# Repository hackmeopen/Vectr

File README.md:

Vectr
=====

Vectr 3D Sensing Controller

Vectr is an open source 3D sensing controller and sequencer. The board files and firmware are here. Vectr software and hardware are released under 
the Modified BSD License. Vectr uses a number of libraries from Microchip which, although they are free to use,are not fully open source. 
The BSD license allows me to release my contributions as free to use while retaining Microchip's copyrights. This arrangement
was worked out in discussions with the legal department of Microchip.

You are free to use Vectr's firmware and hardware for your own purposes.

Vectr uses Microchip Technology's MGC3130 to sense a user's hand in free space above it's surface. It is able to determine the position of the user's hand within a  cubic volume which is 4inx4inx6in. 

Vectr has 36 LEDs which provide visual feedback about where it senses the user's hand.

It is designed to work with Eurorack modular synthesizers, but the underlying technology can be used for controlling just about anything which will receive an analog voltage input.

Vectr has lots of nifty features for recording sequences of hand movements and playing them back. The sequences can be manipulated as they are played with all sorts of different behaviors. These are the things that make Vectr really special.

So, the code's all there. Vectr uses a PIC32 microcontroller running FreeRTOS. 
There's a lot going on but I've tried to comparmentalize it the best I can. So get started, use it, tweak it, build it!

Cheers

Matt

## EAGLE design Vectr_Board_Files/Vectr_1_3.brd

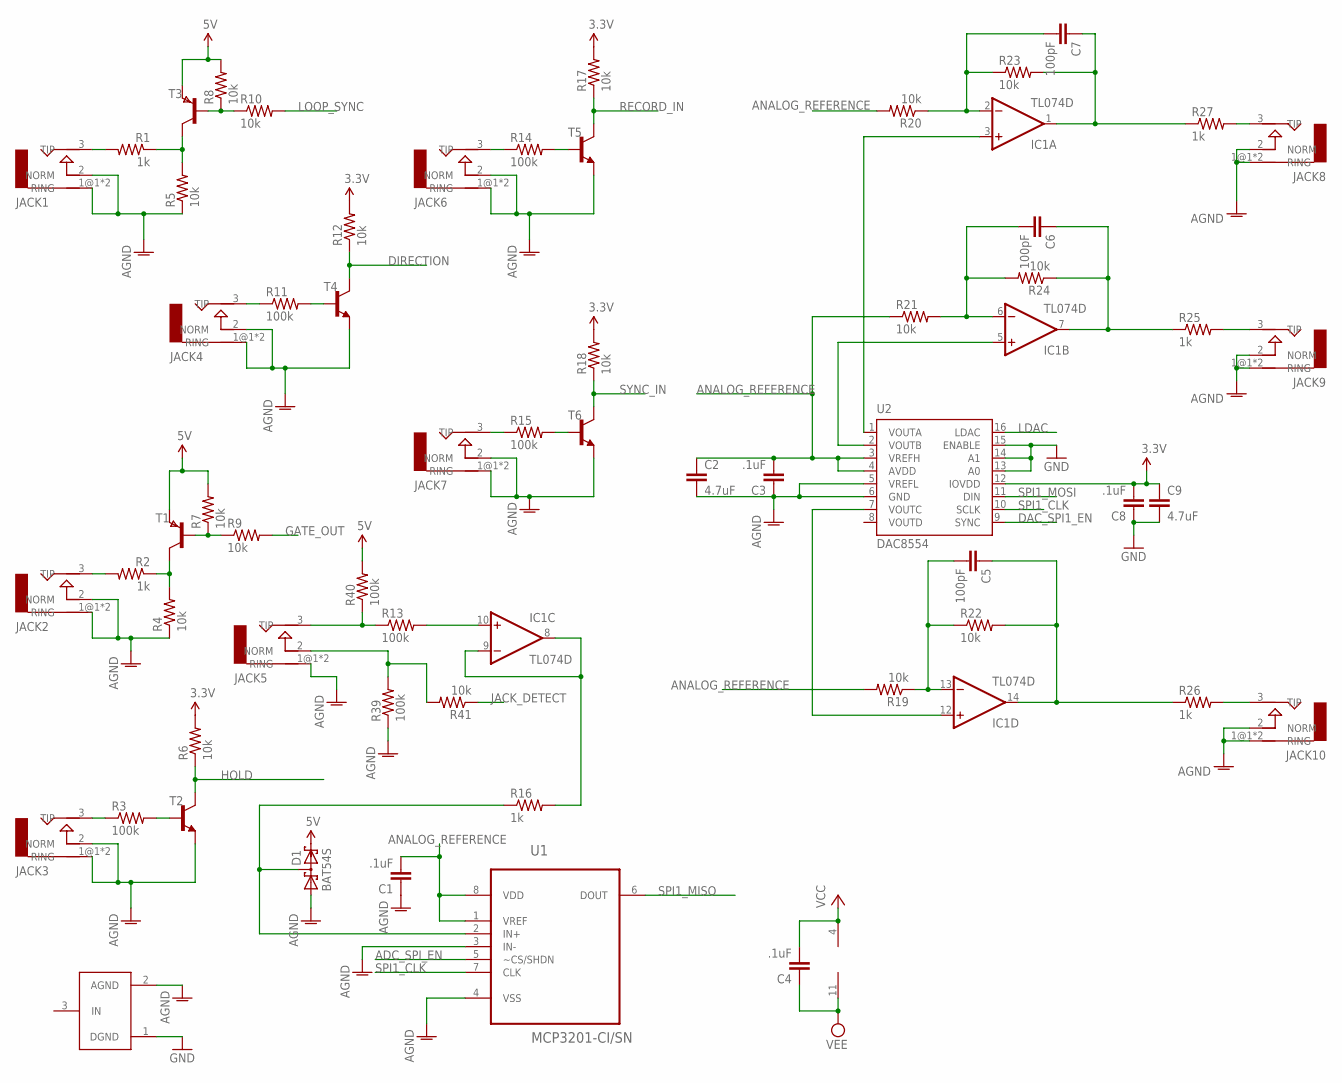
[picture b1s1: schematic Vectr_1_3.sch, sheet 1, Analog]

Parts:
C1, C3, C4, C8: .1uF; 0402-CAP
C2, C9: 4.7uF; 0805
C5, C6, C7: 100pF; 0402-CAP
D1: BAT54S; SOT23
GND_CONNECT: GND_CONNECT
IC1: TL074D; SO14
JACK1, JACK2, JACK3, JACK4, JACK5, JACK6, JACK7, JACK8, JACK9, JACK10: AUDIO-JACKERTHENVAR; ERTHENVAR-JACK
R1, R2, R16, R25, R26, R27: 1k; 0402-RES
R3, R11, R13, R14, R15, R39, R40: 100k; 0402-RES
R4, R5, R6, R7, R8, R9, R10, R12, R17, R18, R19, R20, R21, R22, R23, R24, R41: 10k; 0402-RES
T1, T3: PNPSOT23; SOT-23
T2, T4, T5, T6: TRANSISTOR_NPNSOT23; SOT23
U1: MCP3201-CI/SN; SOIC127P600X175-8N
U2: DAC8554; PW_R-PDSO-G16

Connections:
3.3V: C8.2, C9.1, R6.2, R12.2, R17.2, R18.2, U2.12 (IOVDD); also elsewhere on the board
5V: D1.2 (C2), R7.2, R8.2, R40.2, T1.2 (E), T3.2 (E); also elsewhere on the board
ADC_SPI_EN: U1.5 (~CS/SHDN); also elsewhere on the board
AGND: C1.1, C2.2, C3.1, D1.1 (A1), GND_CONNECT.2 (AGND), JACK1.1@1 (RING), JACK1.1@2 (RING), JACK1.2 (NORM), JACK2.1@1 (RING), JACK2.1@2 (RING), JACK2.2 (NORM), JACK3.1@1 (RING), JACK3.1@2 (RING), JACK3.2 (NORM), JACK4.1@1 (RING), JACK4.1@2 (RING), JACK4.2 (NORM), JACK5.1@1 (RING), JACK5.1@2 (RING), JACK6.1@1 (RING), JACK6.1@2 (RING), JACK6.2 (NORM), JACK7.1@1 (RING), JACK7.1@2 (RING), JACK7.2 (NORM), JACK8.1@1 (RING), JACK8.1@2 (RING), JACK8.2 (NORM), JACK9.1@1 (RING), JACK9.1@2 (RING), JACK9.2 (NORM), JACK10.1@1 (RING), JACK10.1@2 (RING), JACK10.2 (NORM), R4.1, R5.1, R39.1, T2.2 (E), T4.2 (E), T5.2 (E), T6.2 (E), U1.3 (IN-), U1.4 (VSS), U2.5 (VREFL), U2.6 (GND); also elsewhere on the board
ANALOG_REFERENCE: C1.2, C2.1, C3.2, R19.2, R20.2, R21.1, U1.1 (VREF), U1.8 (VDD), U2.3 (VREFH), U2.4 (AVDD); also elsewhere on the board
DAC_SPI1_EN: U2.9 (SYNC); also elsewhere on the board
DIRECTION: R12.1, T4.3 (C); also elsewhere on the board
GATE_OUT: R9.2; also elsewhere on the board
GND: C8.1, C9.2, GND_CONNECT.1 (DGND), U2.13 (A0), U2.14 (A1), U2.15 (ENABLE); also elsewhere on the board
HOLD: R6.1, T2.3 (C); also elsewhere on the board
JACK_DETECT: R41.1; also elsewhere on the board
LDAC: U2.16 (LDAC); also elsewhere on the board
LOOP_SYNC: R10.2; also elsewhere on the board
unnamed: R8.1, R10.1, T3.3 (B)
unnamed: C7.2, IC1.2 (-IN), R20.1, R23.1
unnamed: IC1.10 (+IN), R13.2
unnamed: C7.1, IC1.1 (OUT), R23.2, R27.1
unnamed: R1.1, R5.2, T3.1 (C)
unnamed: JACK1.3 (TIP), R1.2
unnamed: IC1.5 (+IN), U2.2 (VOUTB)
unnamed: JACK4.3 (TIP), R11.1
unnamed: R11.2, T4.1 (B)
unnamed: IC1.8 (OUT), IC1.9 (-IN), R16.2
unnamed: C6.2, IC1.6 (-IN), R21.2, R24.2
unnamed: R7.1, R9.1, T1.3 (B)
unnamed: R2.1, R4.2, T1.1 (C)
unnamed: JACK2.3 (TIP), R2.2
unnamed: C6.1, IC1.7 (OUT), R24.1, R25.1
unnamed: R3.2, T2.1 (B)
unnamed: JACK3.3 (TIP), R3.1
unnamed: C5.2, IC1.13 (-IN), R19.1, R22.1
unnamed: C5.1, IC1.14 (OUT), R22.2, R26.1
unnamed: JACK5.2 (NORM), R39.2, R41.2
unnamed: IC1.3 (+IN), U2.1 (VOUTA)
unnamed: D1.3 (C1A2), R16.1, U1.2 (IN+)
unnamed: JACK8.3 (TIP), R27.2
unnamed: JACK5.3 (TIP), R13.1, R40.1
unnamed: JACK6.3 (TIP), R14.1
unnamed: JACK9.3 (TIP), R25.2
unnamed: R14.2, T5.1 (B)
unnamed: IC1.12 (+IN), U2.7 (VOUTC)
unnamed: JACK10.3 (TIP), R26.2
unnamed: JACK7.3 (TIP), R15.1
unnamed: R15.2, T6.1 (B)
RECORD_IN: R17.1, T5.3 (C); also elsewhere on the board
SPI1_CLK: U1.7 (CLK), U2.10 (SCLK); also elsewhere on the board
SPI1_MISO: U1.6 (DOUT); also elsewhere on the board
SPI1_MOSI: U2.11 (DIN); also elsewhere on the board
SYNC_IN: R18.1, T6.3 (C); also elsewhere on the board
VCC: C4.2, IC1.4 (V+); also elsewhere on the board
VEE: C4.1, IC1.11 (V-); also elsewhere on the board

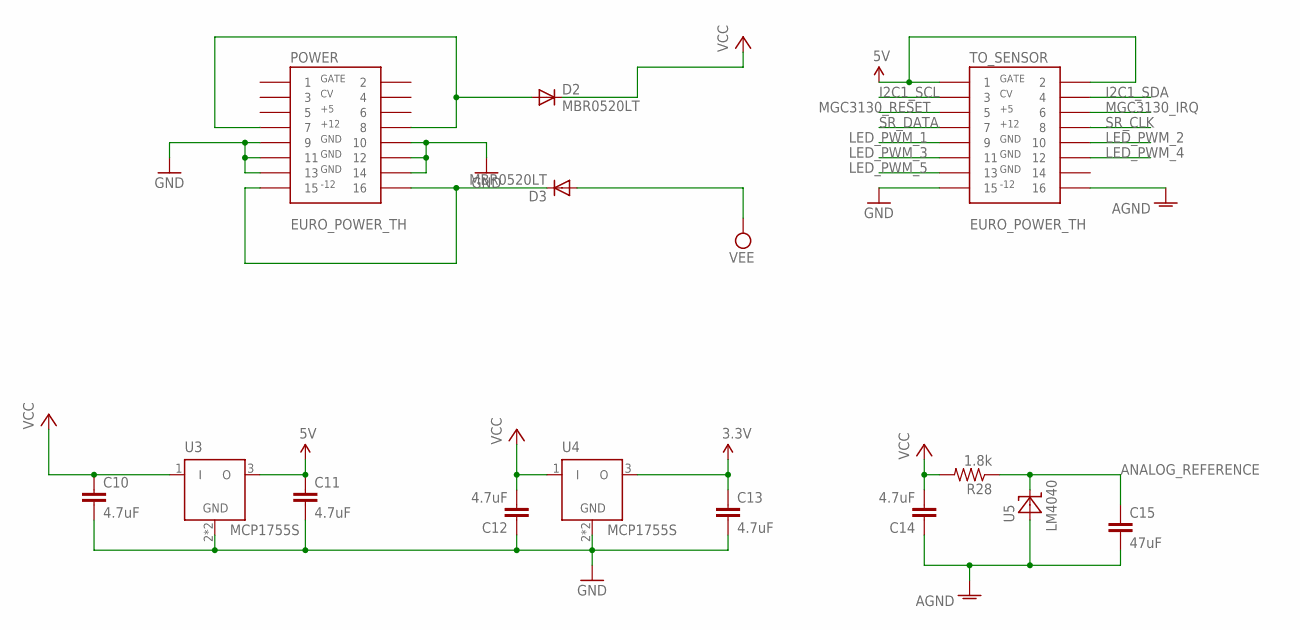
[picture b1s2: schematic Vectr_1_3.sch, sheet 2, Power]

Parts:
C10, C11, C12, C13, C14: 4.7uF; 0805
C15: 47uF; 0805
D2, D3: MBR0520LT; SOD123
POWER: EURO_POWER_TH
R28: 1.8k; 0402-RES
TO_SENSOR: EURO_POWER_TH
U3, U4: MCP1755S; SOT223
U5: LM4040; SOT23

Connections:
3.3V: C13.1, U4.3 (O); also elsewhere on the board
5V: C11.1, TO_SENSOR.1, TO_SENSOR.2, U3.3 (O); also elsewhere on the board
AGND: C14.1, C15.2, TO_SENSOR.16, U5.2 (A); also elsewhere on the board
ANALOG_REFERENCE: C15.1, R28.1, U5.3 (C); also elsewhere on the board
GND: C10.2, C11.2, C12.1, C13.2, POWER.9, POWER.10, POWER.11, POWER.12, POWER.13, POWER.14, TO_SENSOR.15, U3.2 (GND), U3.4 (GND), U4.2 (GND), U4.4 (GND); also elsewhere on the board
I2C1_SCL: TO_SENSOR.3; also elsewhere on the board
I2C1_SDA: TO_SENSOR.4; also elsewhere on the board
LED_PWM_1: TO_SENSOR.9; also elsewhere on the board
LED_PWM_2: TO_SENSOR.10; also elsewhere on the board
LED_PWM_3: TO_SENSOR.11; also elsewhere on the board
LED_PWM_4: TO_SENSOR.12; also elsewhere on the board
LED_PWM_5: TO_SENSOR.13; also elsewhere on the board
MGC3130_IRQ: TO_SENSOR.6; also elsewhere on the board
MGC3130_RESET: TO_SENSOR.5; also elsewhere on the board
unnamed: D2.A, POWER.7, POWER.8
unnamed: D3.C, POWER.15, POWER.16
SR_CLK: TO_SENSOR.8; also elsewhere on the board
SR_DATA: TO_SENSOR.7; also elsewhere on the board
VCC: C10.1, C12.2, C14.2, D2.C, R28.2, U3.1 (I), U4.1 (I); also elsewhere on the board
VEE: D3.A; also elsewhere on the board

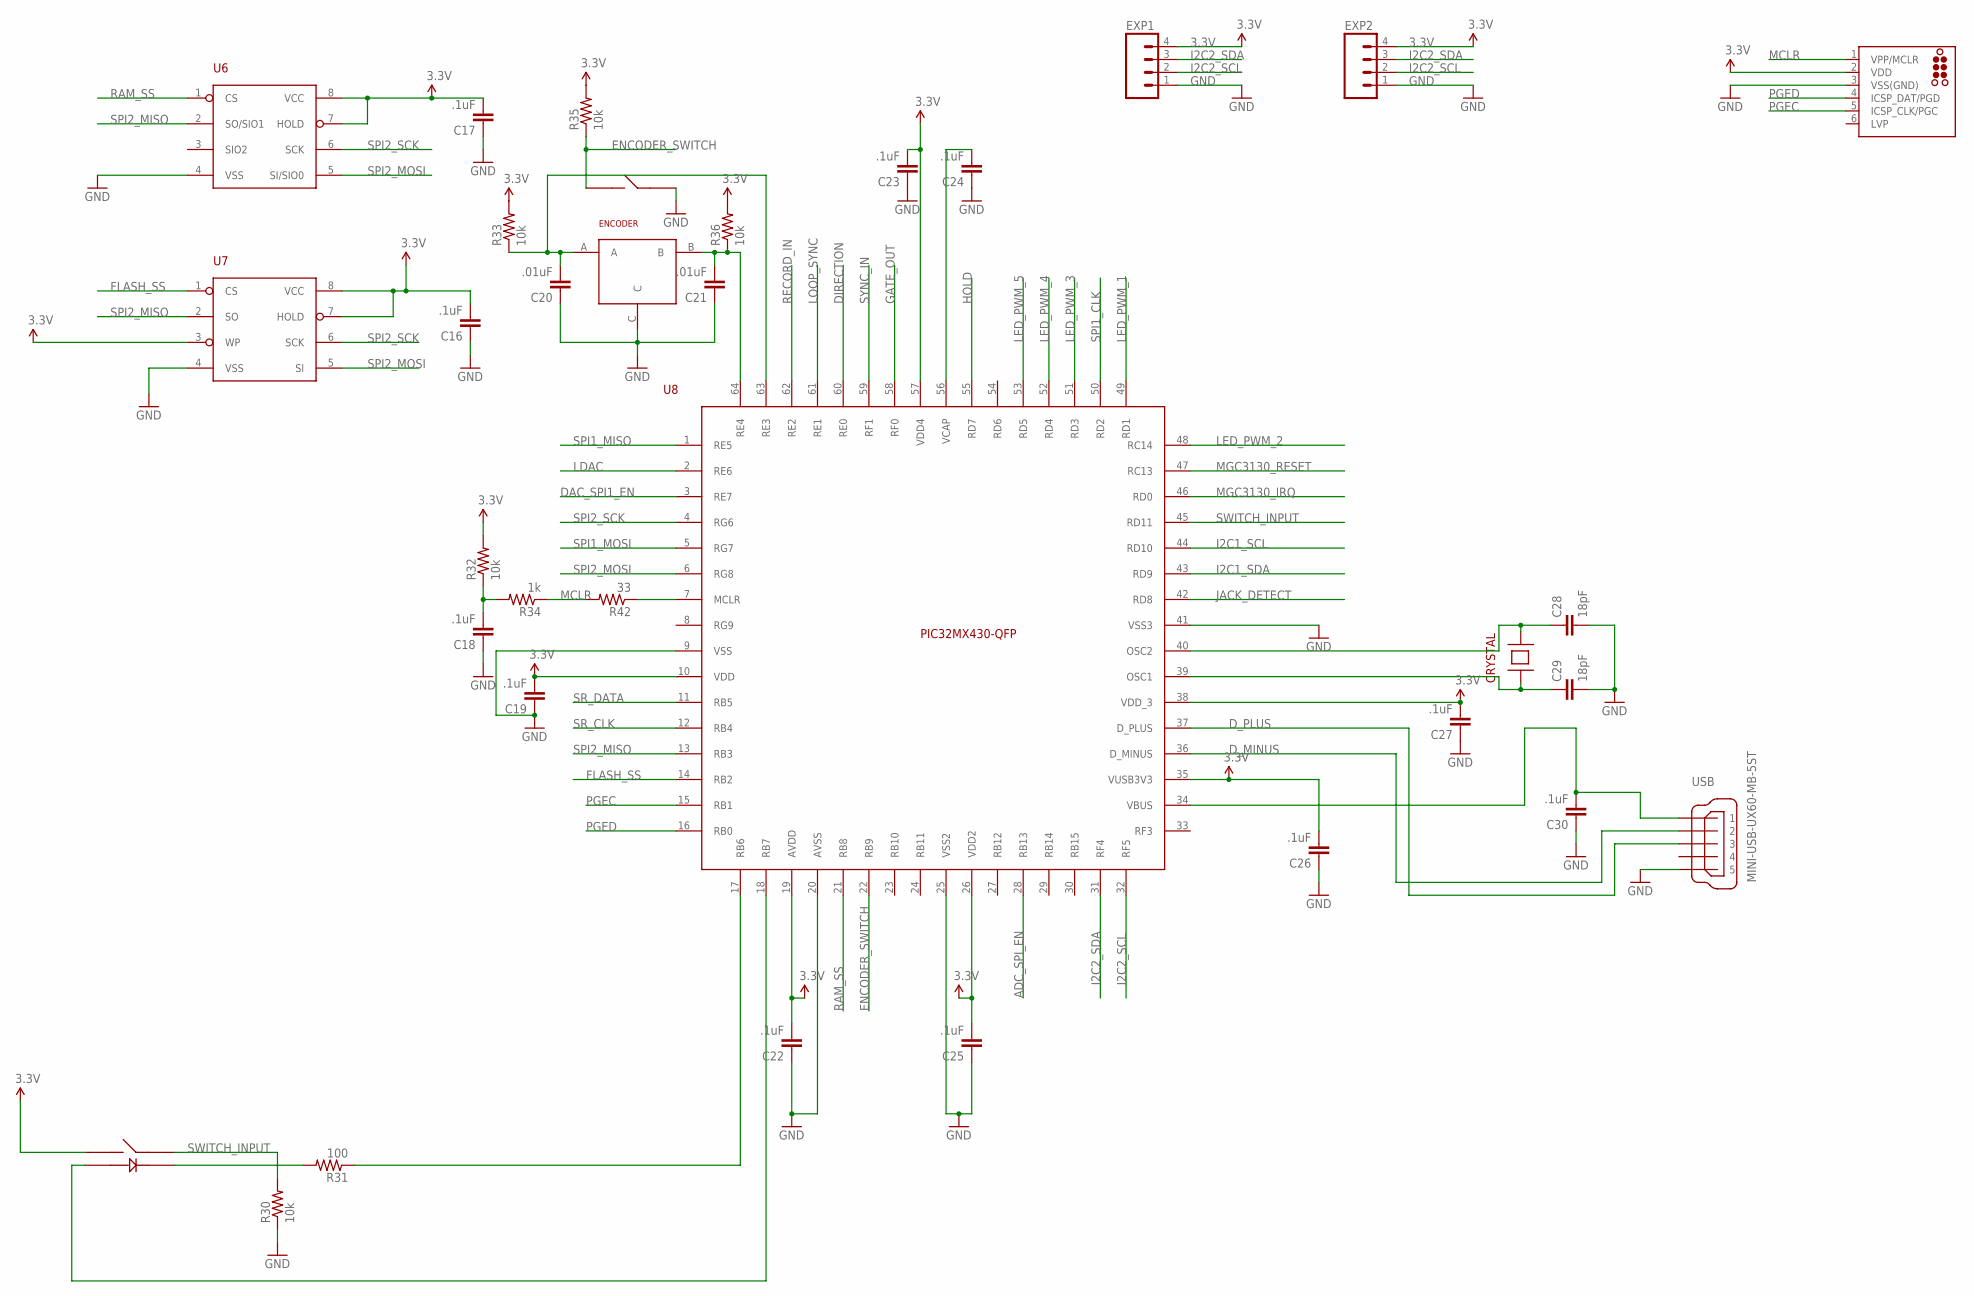
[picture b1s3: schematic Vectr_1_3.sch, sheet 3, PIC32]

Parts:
C16, C17, C18, C19, C22, C23, C24, C25, C26, C27, C30: .1uF; 0402-CAP
C20, C21: .01uF; 0402-CAP
C28, C29: 18pF; 0402-CAP
CRYSTAL: SMD-4-CRYSTAL
ENCODER: PEC16_ENCODER
EXP1, EXP2: M04PTH; 1X04
J1: TC2030-MCP
R30, R32, R33, R35, R36: 10k; 0402-RES
R31: 100; 0402-RES
R34: 1k; 0402-RES
R42: 33; 0402-RES
SWITCH: 5GSH9
U6: 23LC512; SO-08
U7: SST25VF010A; SO-08
U8: PIC32MX430-QFP; QFP50P1200X1200X120-64N
USB: MINI-USB-UX60-MB-5ST; UX60-MB-5ST

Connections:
3.3V: C16.2, C17.2, C19.2, C22.2, C23.2, C25.2, C26.2, C27.2, EXP1.4, EXP2.4, J1.2 (VDD), R32.2, R33.2, R35.2, R36.2, SWITCH.1, U6.7 (HOLD), U6.8 (VCC), U7.3 (WP), U7.7 (HOLD), U7.8 (VCC), U8.10 (VDD), U8.19 (AVDD), U8.26 (VDD2), U8.35 (VUSB3V3), U8.38 (VDD_3), U8.57 (VDD4); also elsewhere on the board
ADC_SPI_EN: U8.28 (RB13); also elsewhere on the board
DAC_SPI1_EN: U8.3 (RE7); also elsewhere on the board
DIRECTION: U8.60 (RE0); also elsewhere on the board
D_MINUS: U8.36 (D_MINUS), USB.2
D_PLUS: U8.37 (D_PLUS), USB.3
ENCODER_SWITCH: ENCODER.D, R35.1, U8.22 (RB9)
FLASH_SS: U7.1 (CS), U8.14 (RB2)
GATE_OUT: U8.58 (RF0); also elsewhere on the board
GND: C16.1, C17.1, C18.1, C19.1, C20.1, C21.1, C22.1, C23.1, C24.1, C25.1, C26.1, C27.1, C28.2, C29.2, C30.1, ENCODER.C, ENCODER.E, EXP1.1, EXP2.1, J1.3 (VSS(GND)), R30.1, U6.4 (VSS), U7.4 (VSS), U8.9 (VSS), U8.20 (AVSS), U8.25 (VSS2), U8.41 (VSS3), USB.5; also elsewhere on the board
HOLD: U8.55 (RD7); also elsewhere on the board
I2C1_SCL: U8.44 (RD10); also elsewhere on the board
I2C1_SDA: U8.43 (RD9); also elsewhere on the board
I2C2_SCL: EXP1.2, EXP2.2, U8.32 (RF5)
I2C2_SDA: EXP1.3, EXP2.3, U8.31 (RF4)
JACK_DETECT: U8.42 (RD8); also elsewhere on the board
LDAC: U8.2 (RE6); also elsewhere on the board
LED_PWM_1: U8.49 (RD1); also elsewhere on the board
LED_PWM_2: U8.48 (RC14); also elsewhere on the board
LED_PWM_3: U8.51 (RD3); also elsewhere on the board
LED_PWM_4: U8.52 (RD4); also elsewhere on the board
LED_PWM_5: U8.53 (RD5); also elsewhere on the board
LOOP_SYNC: U8.61 (RE1); also elsewhere on the board
MCLR: J1.1 (VPP/MCLR), R34.1, R42.2
MGC3130_IRQ: U8.46 (RD0); also elsewhere on the board
MGC3130_RESET: U8.47 (RC13); also elsewhere on the board
unnamed: C18.2, R32.1, R34.2
unnamed: C21.2, ENCODER.B, R36.1, U8.64 (RE4)
unnamed: C20.2, ENCODER.A, R33.1, U8.63 (RE3)
unnamed: SWITCH.3, U8.18 (RB7)
unnamed: C28.1, CRYSTAL.3, U8.40 (OSC2)
unnamed: C29.1, CRYSTAL.1, U8.39 (OSC1)
unnamed: C30.2, U8.34 (VBUS), USB.1
unnamed: C24.2, U8.56 (VCAP)
unnamed: R31.2, SWITCH.2
PGEC: J1.5 (ICSP_CLK/PGC), U8.15 (RB1)
PGED: J1.4 (ICSP_DAT/PGD), U8.16 (RB0)
RAM_SS: U6.1 (CS), U8.21 (RB8)
RECORD_IN: U8.62 (RE2); also elsewhere on the board
RESET: R42.1, U8.7 (MCLR)
SPI1_CLK: U8.50 (RD2); also elsewhere on the board
SPI1_MISO: U8.1 (RE5); also elsewhere on the board
SPI1_MOSI: U8.5 (RG7); also elsewhere on the board
SPI2_MISO: U6.2 (SO/SIO1), U7.2 (SO), U8.13 (RB3)
SPI2_MOSI: U6.5 (SI/SIO0), U7.5 (SI), U8.6 (RG8)
SPI2_SCK: U6.6 (SCK), U7.6 (SCK), U8.4 (RG6)
SR_CLK: U8.12 (RB4); also elsewhere on the board
SR_DATA: U8.11 (RB5); also elsewhere on the board
SWITCH_INPUT: R30.2, SWITCH.4, U8.45 (RD11)
SWITCH_LED1: R31.1, U8.17 (RB6)
SYNC_IN: U8.59 (RF1); also elsewhere on the board

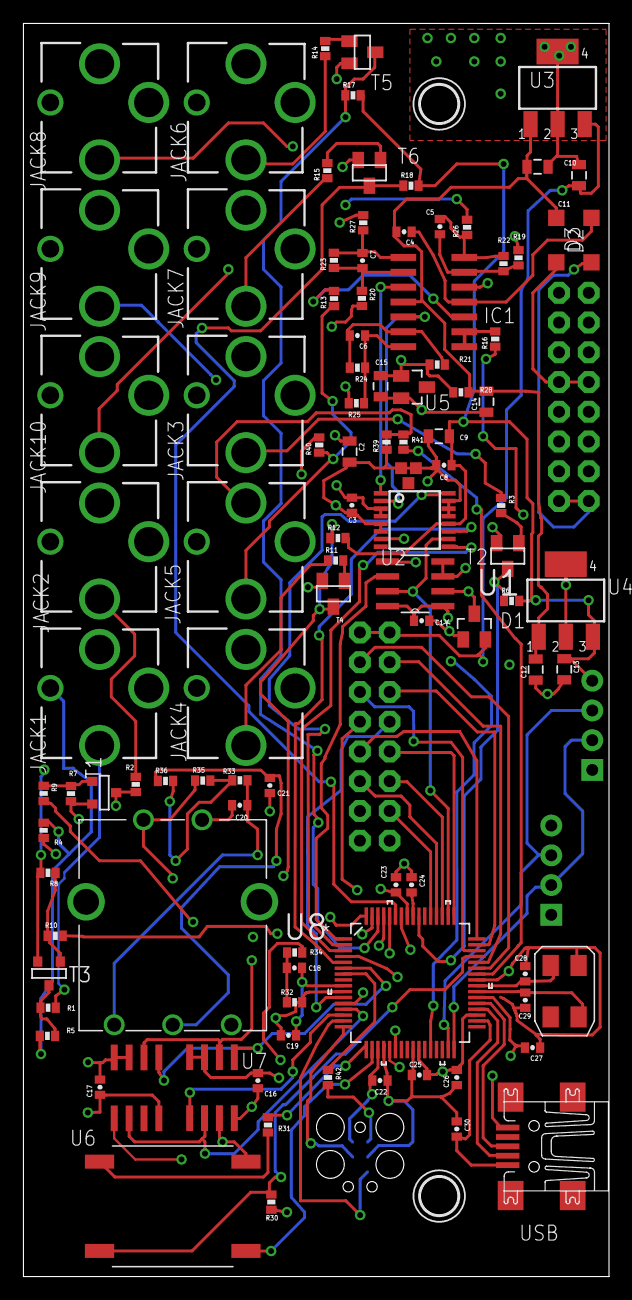
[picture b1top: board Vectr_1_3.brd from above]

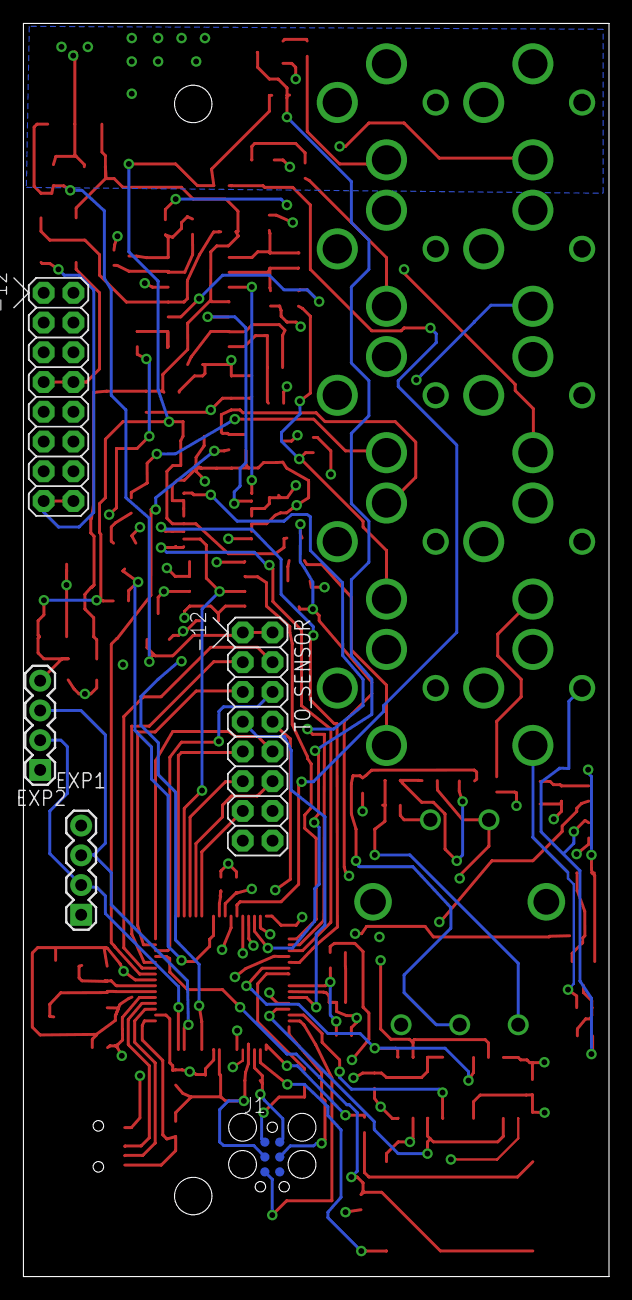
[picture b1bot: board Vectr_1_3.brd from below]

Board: 4 copper layers, 50.0 x 107.0 mm, 109 parts (5 on the bottom side), 89 nets.

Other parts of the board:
U$3, U$5: 3,2

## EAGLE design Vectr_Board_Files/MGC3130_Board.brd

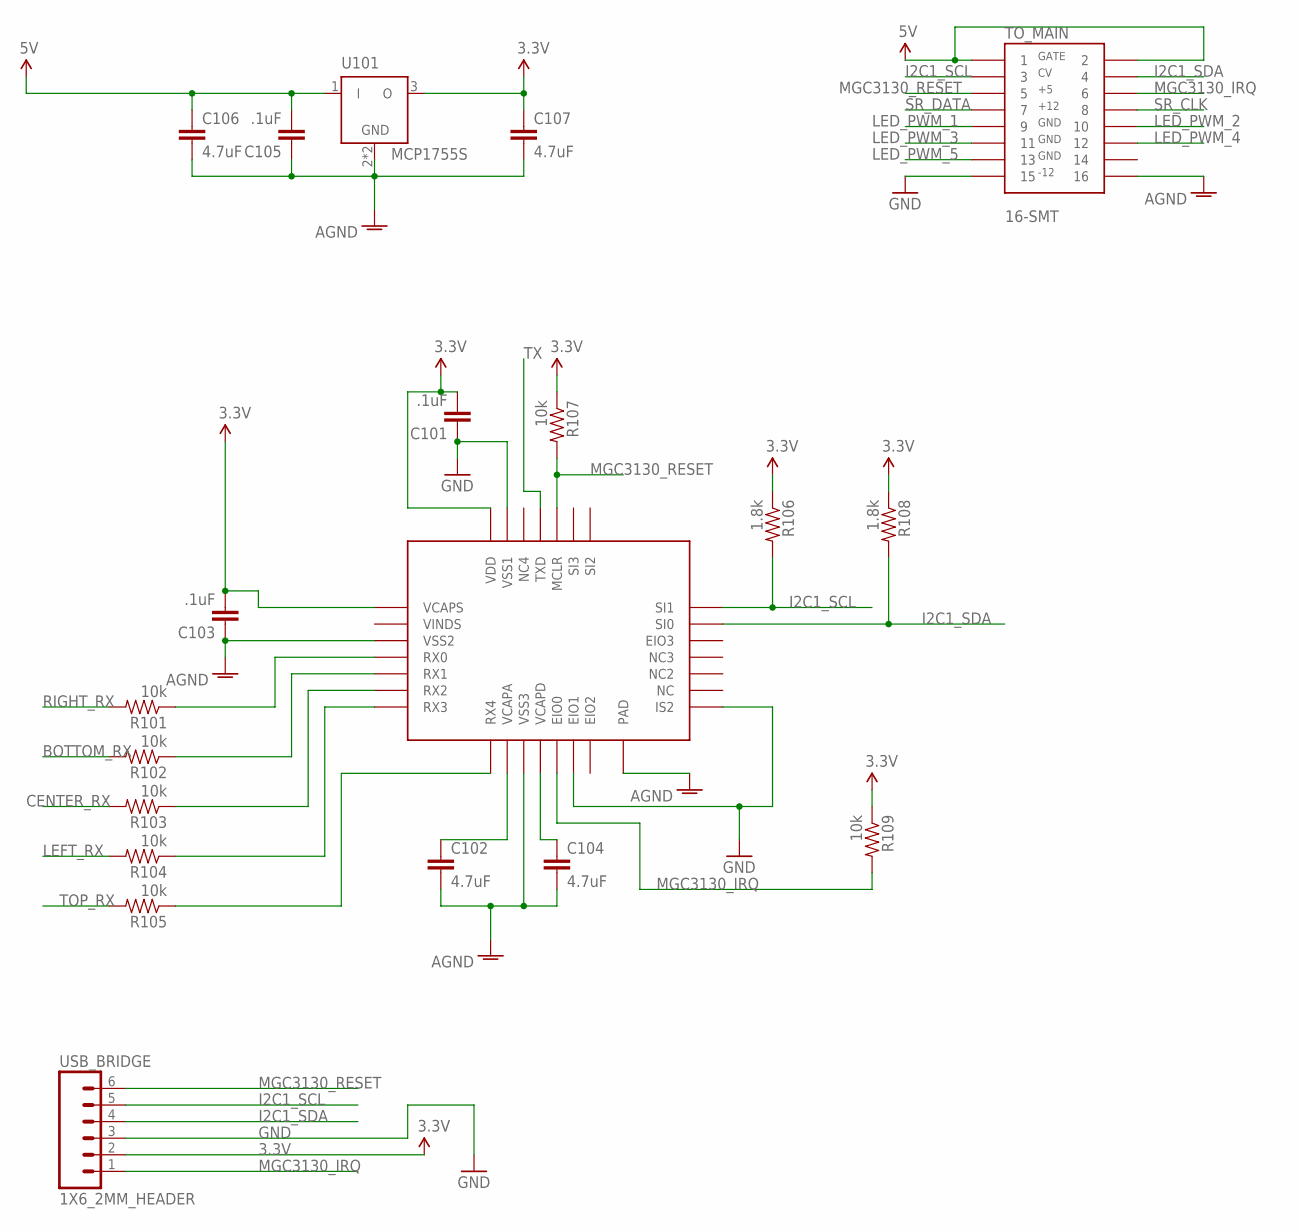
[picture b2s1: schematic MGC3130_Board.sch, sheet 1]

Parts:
C101, C103, C105: .1uF; 0402-CAP
C102, C104, C106, C107: 4.7uF; 0805
R101, R102, R103, R104, R105, R107, R109: 10k; 0402-RES
R106, R108: 1.8k; 0402-RES
TO_MAIN: 16-SMT
U101: MCP1755S; SOT223
U102: MGC3130; QFN28
USB_BRIDGE: 1X6_2MM_HEADER

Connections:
3.3V: C101.2, C103.2, C107.1, R106.1, R107.1, R108.1, R109.1, U101.3 (O), U102.P$1 (VCAPS), U102.P$28 (VDD), USB_BRIDGE.2
5V: C105.2, C106.1, TO_MAIN.P$1 (1), TO_MAIN.P$2 (2), U101.1 (I); also elsewhere on the board
AGND: C102.2, C103.1, C104.2, C105.1, C106.2, C107.2, TO_MAIN.P$16 (16), U101.2 (GND), U101.4 (GND), U102.P$3 (VSS2), U102.P$10 (VSS3), U102.P$29 (PAD)
BOTTOM_RX: R102.2
CENTER_RX: R103.2
GND: C101.1, TO_MAIN.P$15 (15), U102.P$13 (EIO1), U102.P$15 (IS2), U102.P$27 (VSS1), USB_BRIDGE.3; also elsewhere on the board
I2C1_SCL: R106.2, TO_MAIN.P$3 (3), U102.P$21 (SI1), USB_BRIDGE.5
I2C1_SDA: R108.2, TO_MAIN.P$4 (4), U102.P$20 (SI0), USB_BRIDGE.4
LED_PWM_1: TO_MAIN.P$9 (9); also elsewhere on the board
LED_PWM_2: TO_MAIN.P$10 (10); also elsewhere on the board
LED_PWM_3: TO_MAIN.P$11 (11); also elsewhere on the board
LED_PWM_4: TO_MAIN.P$12 (12); also elsewhere on the board
LED_PWM_5: TO_MAIN.P$13 (13); also elsewhere on the board
LEFT_RX: R104.2
MGC3130_IRQ: R109.2, TO_MAIN.P$6 (6), U102.P$12 (EIO0), USB_BRIDGE.1
MGC3130_RESET: R107.2, TO_MAIN.P$5 (5), U102.P$24 (MCLR), USB_BRIDGE.6
unnamed: R101.1, U102.P$4 (RX0)
unnamed: R102.1, U102.P$5 (RX1)
unnamed: R103.1, U102.P$6 (RX2)
unnamed: R104.1, U102.P$7 (RX3)
unnamed: R105.1, U102.P$8 (RX4)
unnamed: C102.1, U102.P$9 (VCAPA)
unnamed: C104.1, U102.P$11 (VCAPD)
RIGHT_RX: R101.2
SR_CLK: TO_MAIN.P$8 (8); also elsewhere on the board
SR_DATA: TO_MAIN.P$7 (7); also elsewhere on the board
TOP_RX: R105.2
TX: U102.P$25 (TXD)

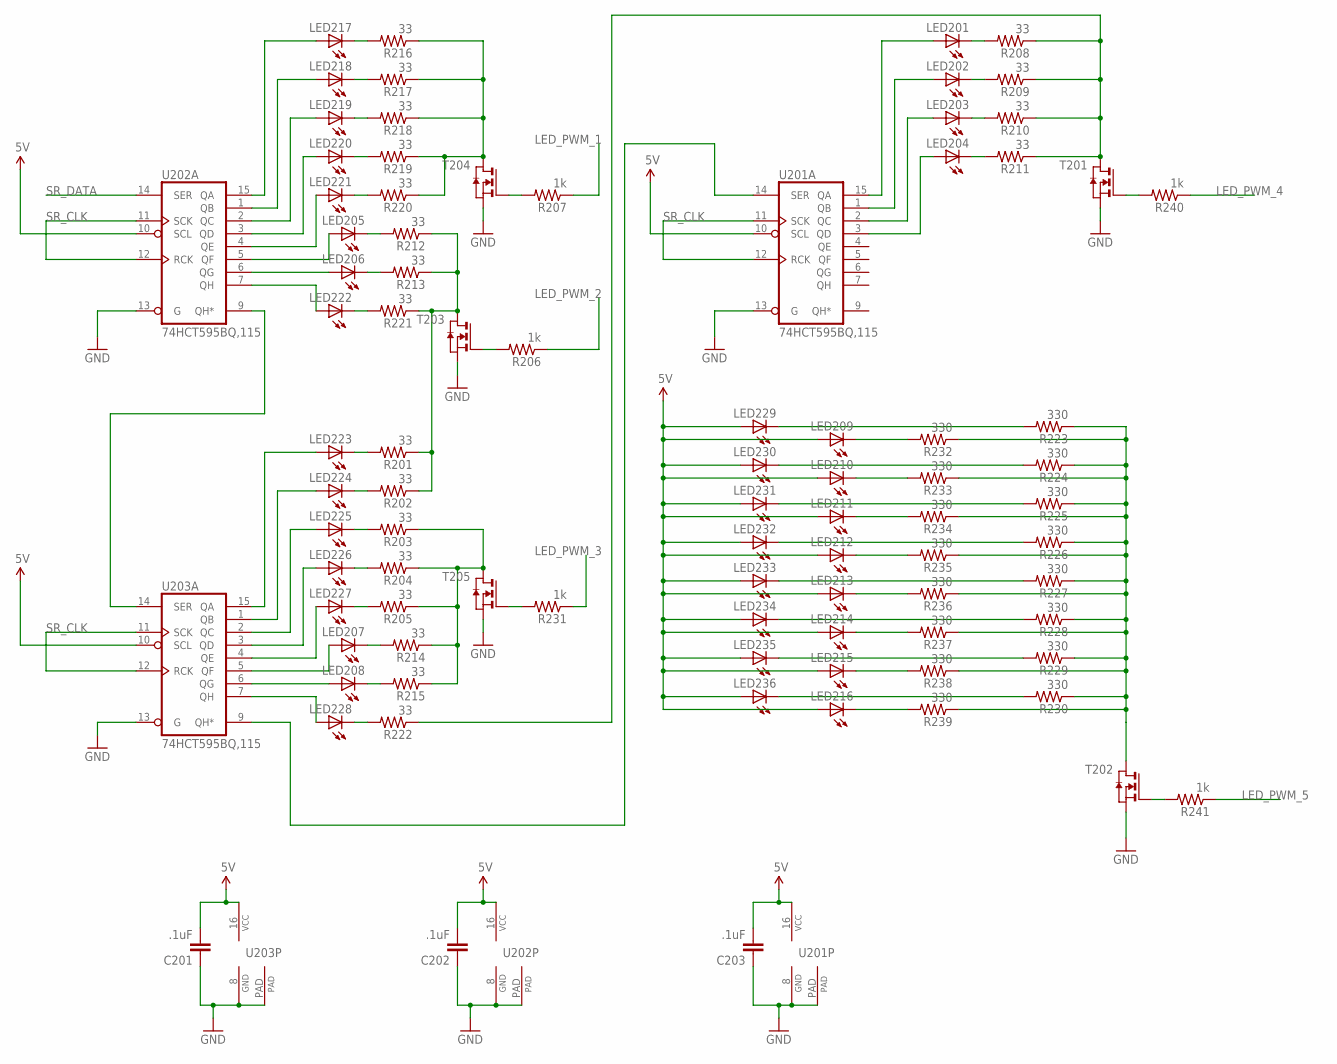
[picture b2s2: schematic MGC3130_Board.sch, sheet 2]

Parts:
C201, C202, C203: .1uF; 0402-CAP
LED201, LED202, LED203, LED204, LED205, LED206, LED207, LED208, LED217, LED218, LED219, LED220, LED221, LED222, LED223, LED224, LED225, LED226, LED227, LED228: APA3010QBC/D-GX; APA3010
LED209, LED210, LED211, LED212, LED213, LED214, LED215, LED216, LED229, LED230, LED231, LED232, LED233, LED234, LED235, LED236: APA3010SRCPRV-GX; APA3010
R201, R202, R203, R204, R205, R208, R209, R210, R211, R212, R213, R214, R215, R216, R217, R218, R219, R220, R221, R222: 33; 0402-RES
R206, R207, R231, R241: 1k; 0402-RES
R223, R224, R225, R226, R227, R228, R229, R230, R232, R233, R234, R235, R236, R237, R238, R239: 330; 0402-RES
R240: 1k; 0603-RES
T201, T202, T203, T204, T205: NMOSSOT23; SOT-23
U201, U202, U203: 74HCT595BQ,115; DHVQFN16

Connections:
5V: C201.2, C202.2, C203.2, LED209.P$2 (A), LED210.P$2 (A), LED211.P$2 (A), LED212.P$2 (A), LED213.P$2 (A), LED214.P$2 (A), LED215.P$2 (A), LED216.P$2 (A), LED229.P$2 (A), LED230.P$2 (A), LED231.P$2 (A), LED232.P$2 (A), LED233.P$2 (A), LED234.P$2 (A), LED235.P$2 (A), LED236.P$2 (A), U201.10 (SCL), U201.16 (VCC), U202.10 (SCL), U202.16 (VCC), U203.10 (SCL), U203.16 (VCC); also elsewhere on the board
GND: C201.1, C202.1, C203.1, T201.2 (S), T202.2 (S), T203.2 (S), T204.2 (S), T205.2 (S), U201.8 (GND), U201.13 (G), U201.PAD (GND1), U202.8 (GND), U202.13 (G), U202.PAD (GND1), U203.8 (GND), U203.13 (G), U203.PAD (GND1); also elsewhere on the board
LED_PWM_1: R207.1; also elsewhere on the board
LED_PWM_2: R206.1; also elsewhere on the board
LED_PWM_3: R231.1; also elsewhere on the board
LED_PWM_4: R240.1; also elsewhere on the board
LED_PWM_5: R241.1; also elsewhere on the board
unnamed: LED229.P$1 (C), R223.2
unnamed: LED209.P$1 (C), R232.2
unnamed: LED230.P$1 (C), R224.2
unnamed: LED210.P$1 (C), R233.2
unnamed: LED231.P$1 (C), R225.2
unnamed: LED208.P$2 (A), U203.6 (QG)
unnamed: LED211.P$1 (C), R234.2
unnamed: LED232.P$1 (C), R226.2
unnamed: LED212.P$1 (C), R235.2
unnamed: LED234.P$1 (C), R228.2
unnamed: LED233.P$1 (C), R227.2
unnamed: LED213.P$1 (C), R236.2
unnamed: LED214.P$1 (C), R237.2
unnamed: LED235.P$1 (C), R229.2
unnamed: LED215.P$1 (C), R238.2
unnamed: R207.2, T204.3 (G)
unnamed: LED236.P$1 (C), R230.2
unnamed: LED216.P$1 (C), R239.2
unnamed: LED217.P$2 (A), U202.15 (QA)
unnamed: LED218.P$2 (A), U202.1 (QB)
unnamed: LED219.P$2 (A), U202.2 (QC)
unnamed: LED220.P$2 (A), U202.3 (QD)
unnamed: LED221.P$2 (A), U202.4 (QE)
unnamed: LED205.P$2 (A), U202.5 (QF)
unnamed: LED206.P$2 (A), U202.6 (QG)
unnamed: LED222.P$2 (A), U202.7 (QH)
unnamed: LED217.P$1 (C), R216.2
unnamed: LED218.P$1 (C), R217.2
unnamed: LED219.P$1 (C), R218.2
unnamed: LED220.P$1 (C), R219.2
unnamed: LED221.P$1 (C), R220.2
unnamed: LED205.P$1 (C), R212.2
unnamed: LED206.P$1 (C), R213.2
unnamed: LED222.P$1 (C), R221.2
unnamed: R216.1, R217.1, R218.1, R219.1, R220.1, T204.1 (D)
unnamed: R201.1, R202.1, R212.1, R213.1, R221.1, T203.1 (D)
unnamed: LED223.P$2 (A), U203.15 (QA)
unnamed: LED224.P$2 (A), U203.1 (QB)
unnamed: LED225.P$2 (A), U203.2 (QC)
unnamed: LED226.P$2 (A), U203.3 (QD)
unnamed: LED227.P$2 (A), U203.4 (QE)
unnamed: LED207.P$2 (A), U203.5 (QF)
unnamed: LED228.P$2 (A), U203.7 (QH)
unnamed: LED223.P$1 (C), R201.2
unnamed: LED224.P$1 (C), R202.2
unnamed: LED225.P$1 (C), R203.2
unnamed: LED226.P$1 (C), R204.2
unnamed: LED227.P$1 (C), R205.2
unnamed: LED207.P$1 (C), R214.2
unnamed: LED208.P$1 (C), R215.2
unnamed: LED228.P$1 (C), R222.2
unnamed: R203.1, R204.1, R205.1, R214.1, R215.1, T205.1 (D)
unnamed: LED201.P$2 (A), U201.15 (QA)
unnamed: LED202.P$2 (A), U201.1 (QB)
unnamed: LED203.P$2 (A), U201.2 (QC)
unnamed: LED204.P$2 (A), U201.3 (QD)
unnamed: R223.1, R224.1, R225.1, R226.1, R227.1, R228.1, R229.1, R230.1, R232.1, R233.1, R234.1, R235.1, R236.1, R237.1, R238.1, R239.1, T202.1 (D)
unnamed: U202.9 (QH*), U203.14 (SER)
unnamed: LED201.P$1 (C), R208.2
unnamed: LED202.P$1 (C), R209.2
unnamed: LED203.P$1 (C), R210.2
unnamed: LED204.P$1 (C), R211.2
unnamed: R208.1, R209.1, R210.1, R211.1, R222.1, T201.1 (D)
unnamed: U201.14 (SER), U203.9 (QH*)
unnamed: R206.2, T203.3 (G)
unnamed: R231.2, T205.3 (G)
unnamed: R240.2, T201.3 (G)
unnamed: R241.2, T202.3 (G)
SR_CLK: U201.11 (SCK), U201.12 (RCK), U202.11 (SCK), U202.12 (RCK), U203.11 (SCK), U203.12 (RCK); also elsewhere on the board
SR_DATA: U202.14 (SER); also elsewhere on the board

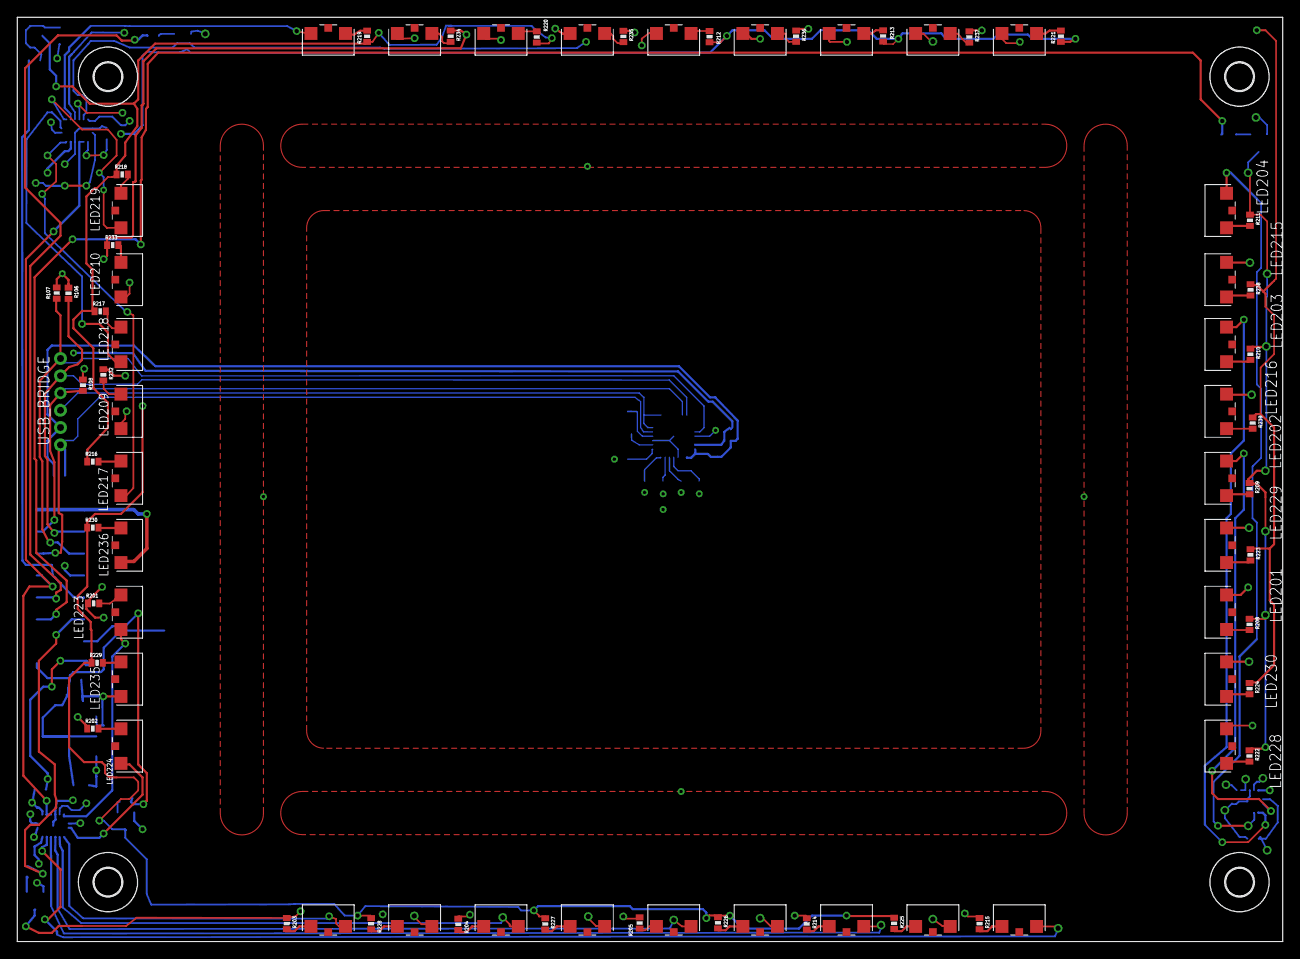
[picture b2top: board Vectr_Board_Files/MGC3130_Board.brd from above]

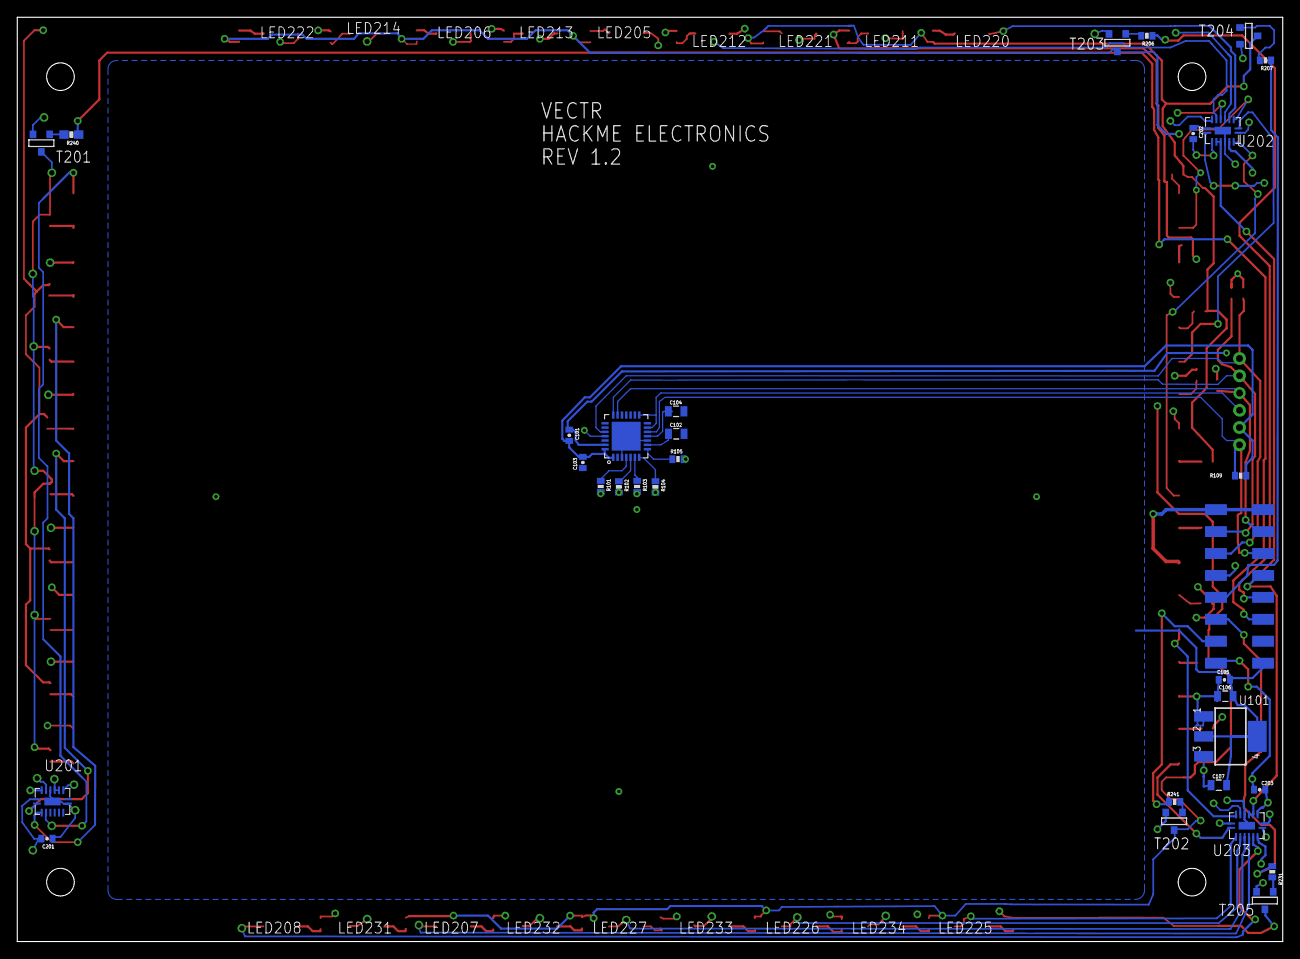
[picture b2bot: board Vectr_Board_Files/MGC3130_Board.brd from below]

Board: 4 copper layers, 146.5 x 107.0 mm, 112 parts (32 on the bottom side), 90 nets.

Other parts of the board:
U$1, U$2, U$3, U$4: 3,2

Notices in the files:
Vectr_Firmware/system_config.h:
Copyright (c) 2013 released Microchip Technology Inc.  All rights reserved.
parts and their libraries:
SparkFun-Passives: Licensing: CC v3.0 Share-Alike You are welcome to use this library for commercial purposes.
tag-connect: ©2009 ROFA.cz - modified and updated by Robert Darlington ‹rdarlington@gmail.com›
